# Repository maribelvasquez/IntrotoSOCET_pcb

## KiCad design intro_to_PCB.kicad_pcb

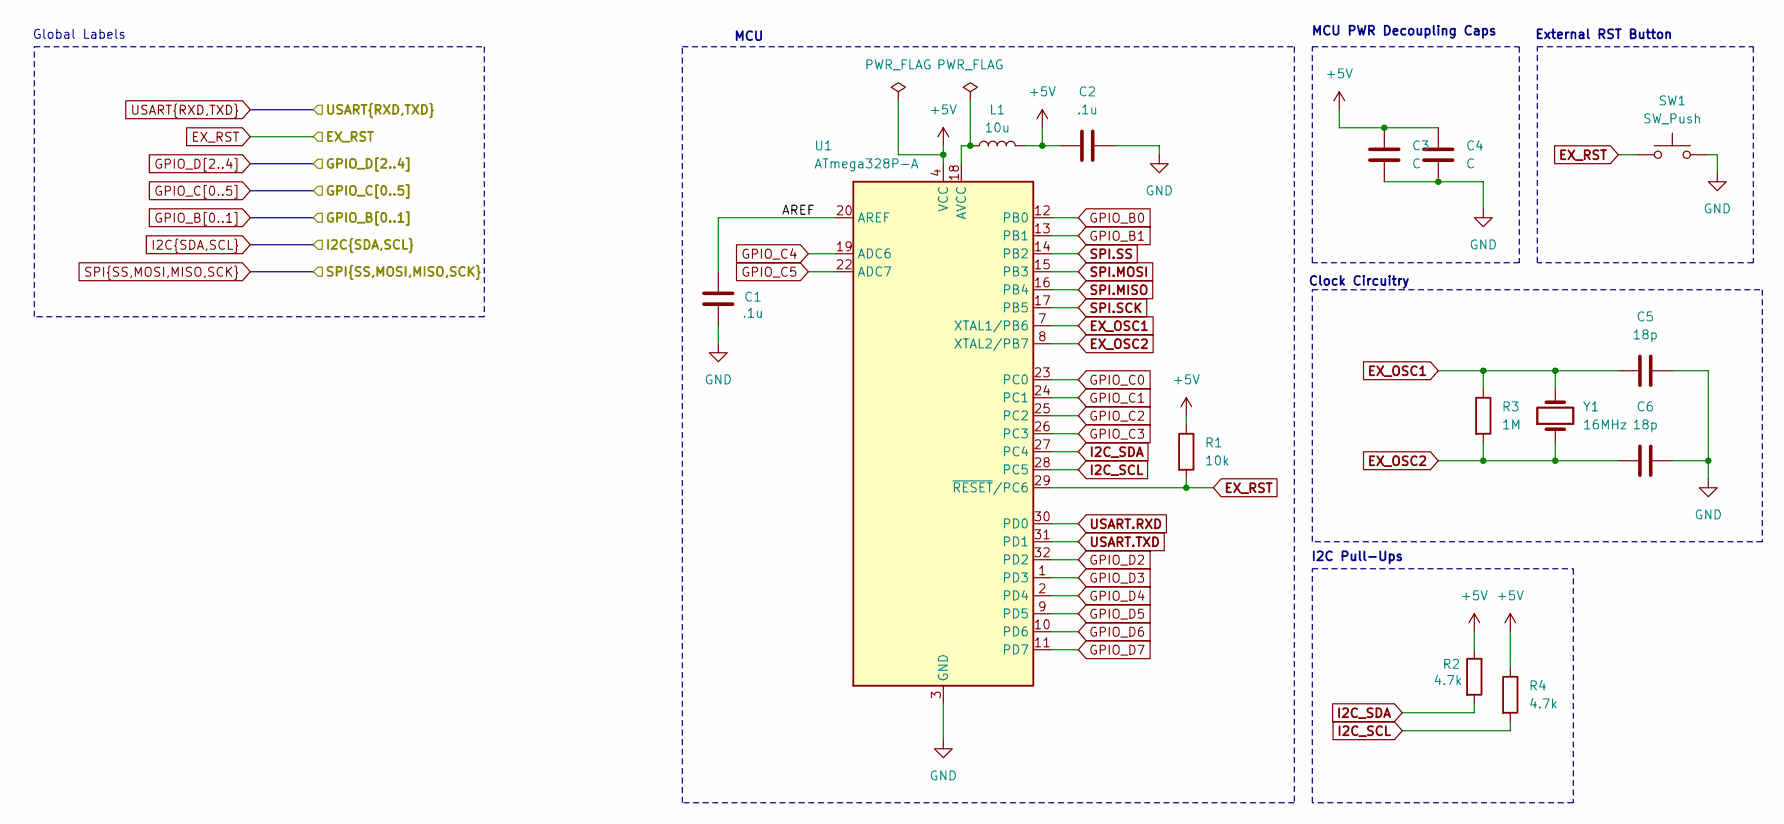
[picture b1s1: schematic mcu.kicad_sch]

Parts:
C1, C2: .1u
C3, C4: C
C5, C6: 18p
L1: 10u
R1: 10k
R2, R4: 4.7k
R3: 1M
SW1: SW_Push
U1: ATmega328P-A; TQFP-32_7x7mm_P0.8mm
Y1: 16MHz

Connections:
+5V: C2.1, C3.1, C4.1, L1.2, R1.1, R2.1, R4.1, U1.4 (VCC), U1.6 (VCC); also elsewhere on the board
/MCU/AREF: C1.1, U1.20 (AREF)
EX_OSC1: C5.1, R3.1, U1.7 (XTAL1/PB6), Y1.2
EX_OSC2: C6.1, R3.2, U1.8 (XTAL2/PB7), Y1.1
EX_RST: R1.2, SW1.1, U1.29 (~RESET/PC6); also elsewhere on the board
GND: C1.2, C2.2, C3.2, C4.2, C5.2, C6.2, SW1.2, U1.3 (GND), U1.5 (GND), U1.21 (GND); also elsewhere on the board
GPIO_B0: U1.12 (PB0); also elsewhere on the board
GPIO_B1: U1.13 (PB1); also elsewhere on the board
GPIO_C0: U1.23 (PC0); also elsewhere on the board
GPIO_C1: U1.24 (PC1); also elsewhere on the board
GPIO_C2: U1.25 (PC2); also elsewhere on the board
GPIO_C3: U1.26 (PC3); also elsewhere on the board
GPIO_C4: U1.19 (ADC6); also elsewhere on the board
GPIO_C5: U1.22 (ADC7); also elsewhere on the board
GPIO_D2: U1.32 (PD2); also elsewhere on the board
GPIO_D3: U1.1 (PD3); also elsewhere on the board
GPIO_D4: U1.2 (PD4); also elsewhere on the board
GPIO_D5: U1.9 (PD5); also elsewhere on the board
GPIO_D6: U1.10 (PD6); also elsewhere on the board
GPIO_D7: U1.11 (PD7); also elsewhere on the board
I2C_SCL: R4.2, U1.28 (PC5); also elsewhere on the board
I2C_SDA: R2.2, U1.27 (PC4); also elsewhere on the board
unnamed: L1.1, U1.18 (AVCC)
SPI.MISO: U1.16 (PB4); also elsewhere on the board
SPI.MOSI: U1.15 (PB3); also elsewhere on the board
SPI.SCK: U1.17 (PB5); also elsewhere on the board
SPI.SS: U1.14 (PB2); also elsewhere on the board
USART.RXD: U1.30 (PD0); also elsewhere on the board
USART.TXD: U1.31 (PD1); also elsewhere on the board

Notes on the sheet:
MCU PWR Decoupling Caps
I2C Pull-Ups
Clock Circuitry
MCU
External RST Button
Global Labels

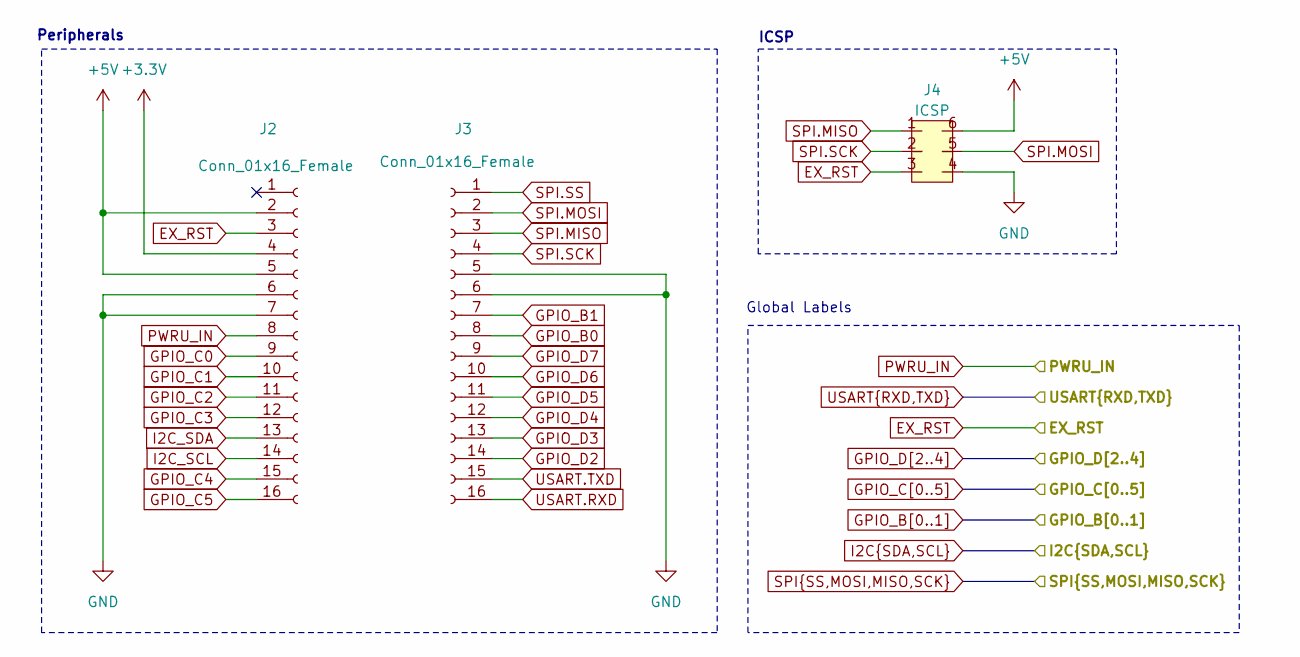
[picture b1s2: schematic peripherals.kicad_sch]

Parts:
J2, J3: Conn_01x16_Female
J4: ICSP

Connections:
+3.3V: J2.4; also elsewhere on the board
+5V: J2.2, J2.5, J4.6; also elsewhere on the board
EX_RST: J2.3, J4.3; also elsewhere on the board
GND: J2.6, J2.7, J3.5, J3.6, J4.4; also elsewhere on the board
GPIO_B0: J3.8; also elsewhere on the board
GPIO_B1: J3.7; also elsewhere on the board
GPIO_C0: J2.9; also elsewhere on the board
GPIO_C1: J2.10; also elsewhere on the board
GPIO_C2: J2.11; also elsewhere on the board
GPIO_C3: J2.12; also elsewhere on the board
GPIO_C4: J2.15; also elsewhere on the board
GPIO_C5: J2.16; also elsewhere on the board
GPIO_D2: J3.14; also elsewhere on the board
GPIO_D3: J3.13; also elsewhere on the board
GPIO_D4: J3.12; also elsewhere on the board
GPIO_D5: J3.11; also elsewhere on the board
GPIO_D6: J3.10; also elsewhere on the board
GPIO_D7: J3.9; also elsewhere on the board
I2C_SCL: J2.14; also elsewhere on the board
I2C_SDA: J2.13; also elsewhere on the board
PWRU_IN: J2.8; also elsewhere on the board
SPI.MISO: J3.3, J4.1; also elsewhere on the board
SPI.MOSI: J3.2, J4.5; also elsewhere on the board
SPI.SCK: J3.4, J4.2; also elsewhere on the board
SPI.SS: J3.1; also elsewhere on the board
USART.RXD: J3.16; also elsewhere on the board
USART.TXD: J3.15; also elsewhere on the board

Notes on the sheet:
ICSP
Global Labels
Peripherals

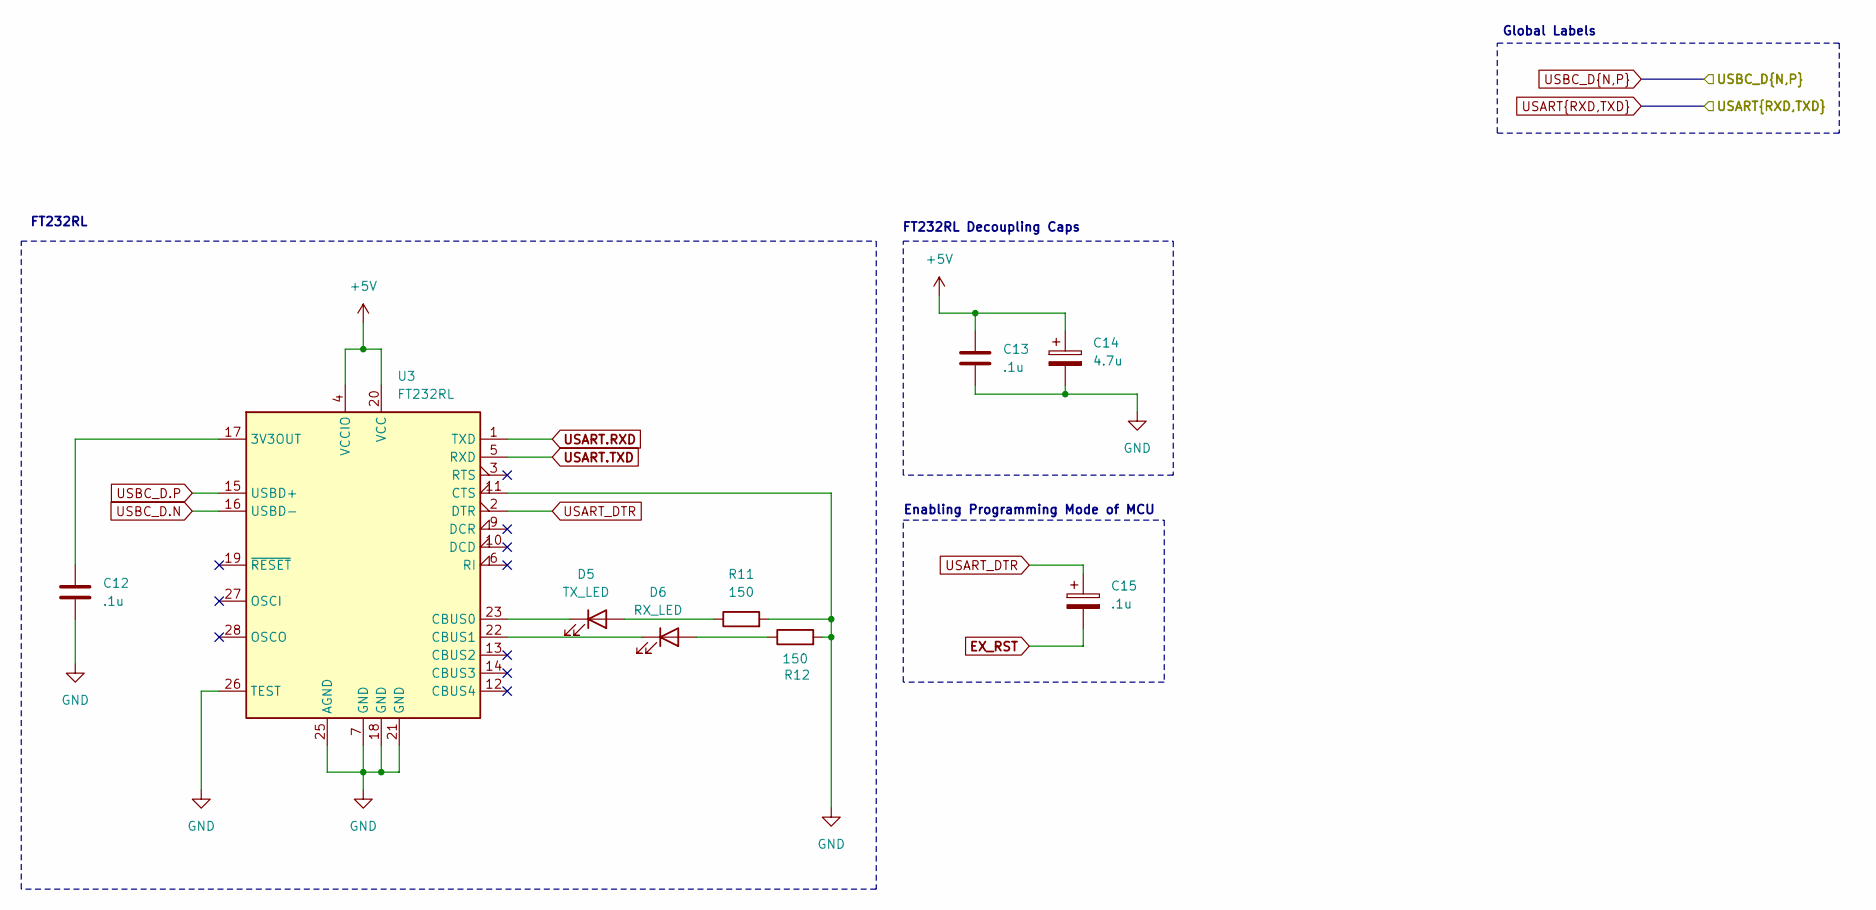
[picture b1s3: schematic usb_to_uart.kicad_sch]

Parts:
C12, C13, C15: .1u
C14: 4.7u
D5: TX_LED
D6: RX_LED
R11, R12: 150
U3: FT232RL; SSOP-28_5.3x10.2mm_P0.65mm

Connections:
+5V: C13.1, C14.1, U3.4 (VCCIO), U3.20 (VCC); also elsewhere on the board
EX_RST: C15.2; also elsewhere on the board
GND: C12.2, C13.2, C14.2, R11.2, R12.2, U3.7 (GND), U3.11 (CTS), U3.18 (GND), U3.21 (GND), U3.25 (AGND), U3.26 (TEST); also elsewhere on the board
unnamed: D5.2 (A), R11.1
unnamed: D5.1 (K), U3.23 (CBUS0)
unnamed: D6.2 (A), R12.1
unnamed: D6.1 (K), U3.22 (CBUS1)
unnamed: C12.1, U3.17 (3V3OUT)
USART.RXD: U3.1 (TXD); also elsewhere on the board
USART.TXD: U3.5 (RXD); also elsewhere on the board
USART_DTR: C15.1, U3.2 (DTR)
USBC_D.N: U3.16 (USBD-); also elsewhere on the board
USBC_D.P: U3.15 (USBD+); also elsewhere on the board

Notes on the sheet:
FT232RL Decoupling Caps
Global Labels
FT232RL
Enabling Programming Mode of MCU

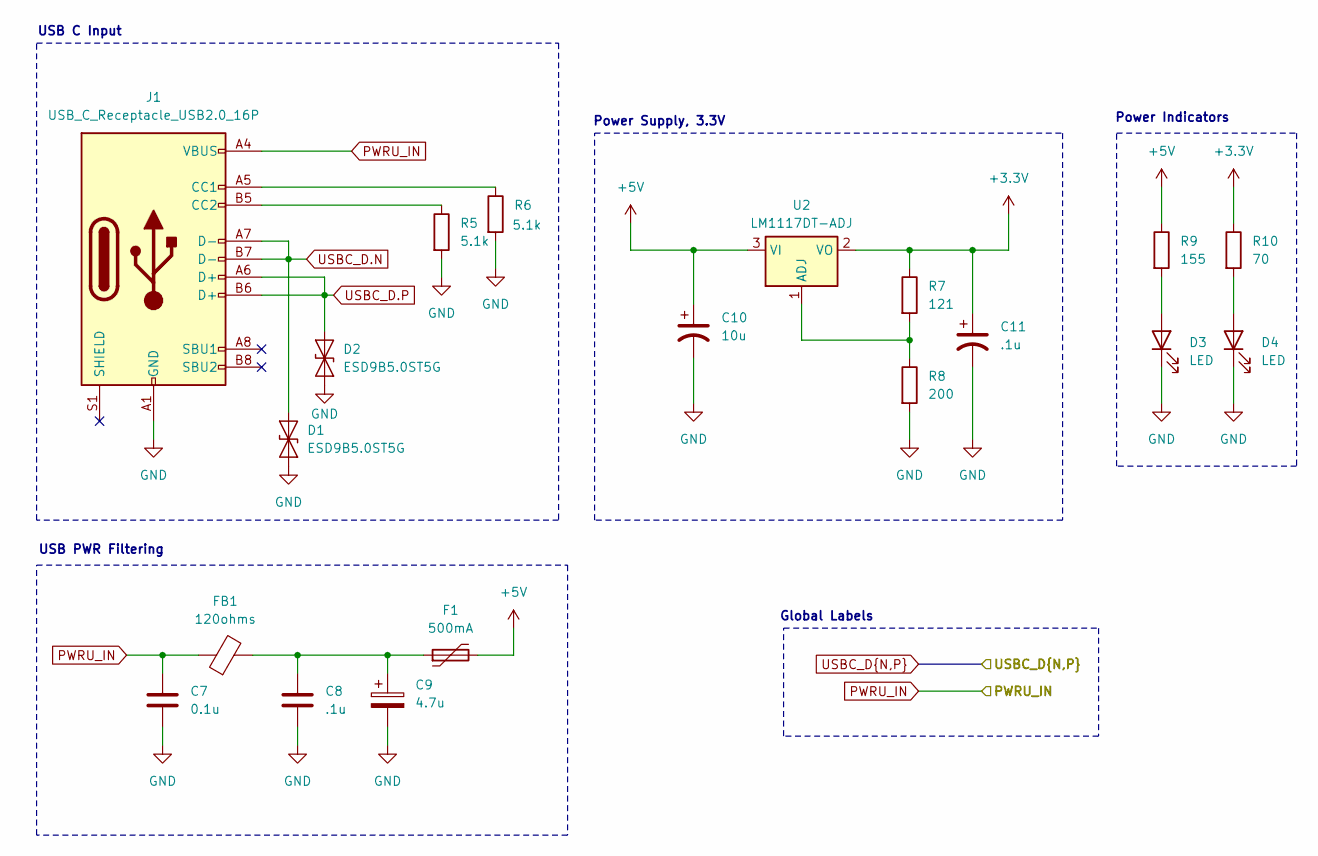
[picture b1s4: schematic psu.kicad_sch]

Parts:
C7: 0.1u
C8, C11: .1u
C9: 4.7u
C10: 10u
D1, D2: ESD9B5.0ST5G; D_SOD-923
D3, D4: LED
F1: 500mA
FB1: 120ohms
J1: USB_C_Receptacle_USB2.0_16P
R5, R6: 5.1k
R7: 121
R8: 200
R9: 155
R10: 70
U2: LM1117DT-ADJ; TO-252-3_TabPin2

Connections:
+3.3V: C11.1, R7.1, R10.1, U2.2 (VO); also elsewhere on the board
+5V: C10.1, F1.2, R9.1, U2.3 (VI); also elsewhere on the board
GND: C7.2, C8.2, C9.2, C10.2, C11.2, D1.1 (A1), D2.2 (A2), D3.1 (K), D4.1 (K), J1.A1 (GND), J1.A12 (GND), J1.B1 (GND), J1.B12 (GND), R5.2, R6.2, R8.2; also elsewhere on the board
unnamed: C8.1, C9.1, F1.1, FB1.2
unnamed: D3.2 (A), R9.2
unnamed: D4.2 (A), R10.2
unnamed: J1.A5 (CC1), R6.1
unnamed: J1.B5 (CC2), R5.1
unnamed: R7.2, R8.1, U2.1 (ADJ)
PWRU_IN: C7.1, FB1.1, J1.A4 (VBUS), J1.A9 (VBUS), J1.B4 (VBUS), J1.B9 (VBUS); also elsewhere on the board
USBC_D.N: D1.2 (A2), J1.A7 (D-), J1.B7 (D-); also elsewhere on the board
USBC_D.P: D2.1 (A1), J1.A6 (D+), J1.B6 (D+); also elsewhere on the board

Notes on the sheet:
Power Indicators
USB PWR Filtering
Global Labels
USB C Input
Power Supply, 3.3V

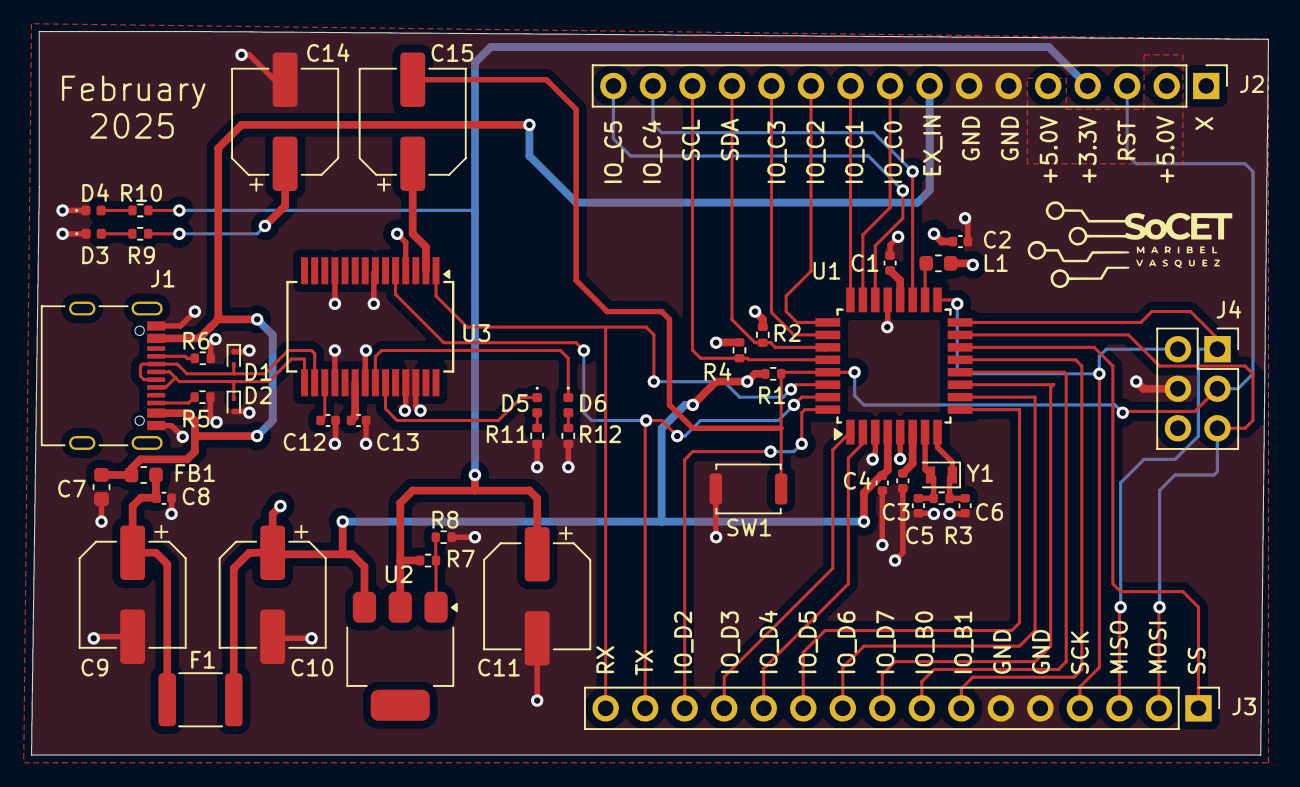
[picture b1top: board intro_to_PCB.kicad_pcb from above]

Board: 2 copper layers, 79.5 x 46.5 mm, 45 parts (0 on the bottom side), 45 nets.
